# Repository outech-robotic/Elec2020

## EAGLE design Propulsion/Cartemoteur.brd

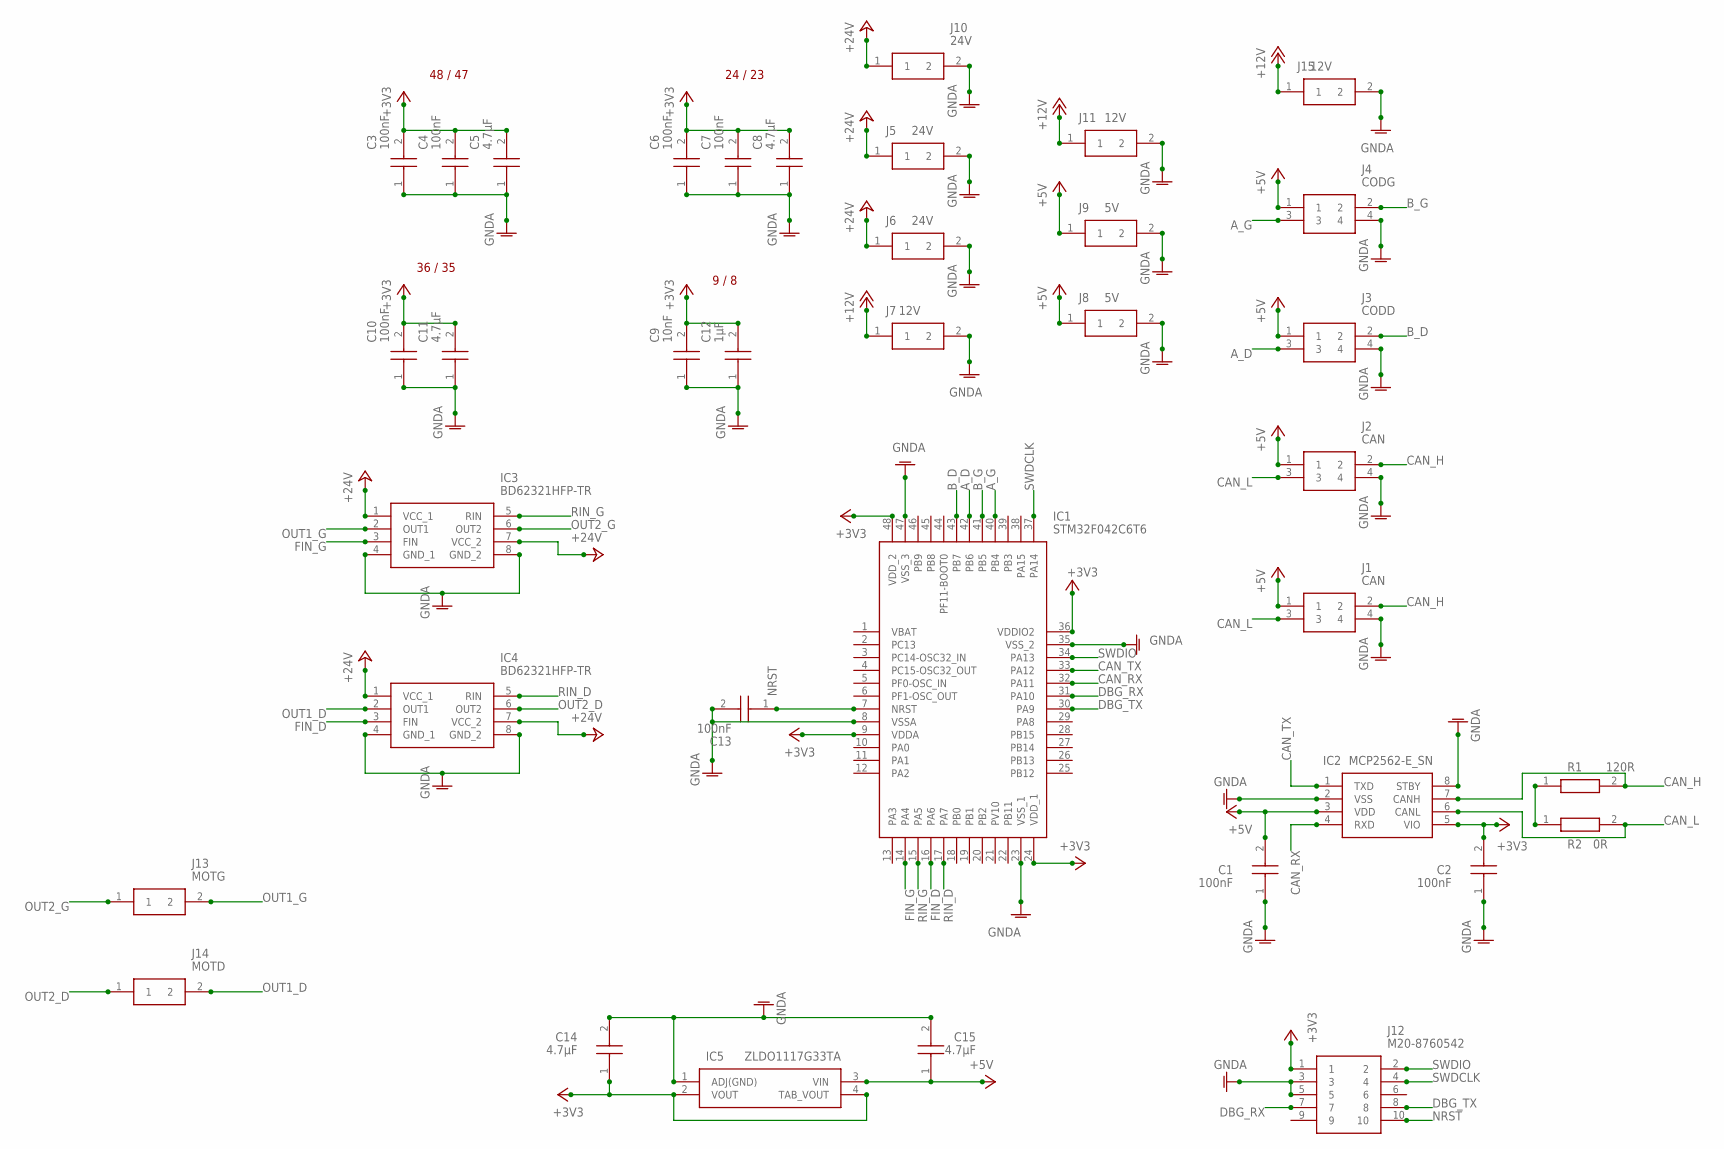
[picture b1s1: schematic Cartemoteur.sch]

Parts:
C1, C2, C3, C4, C6, C7, C10, C13: 100nF; CAPC1608X90N
C5, C8, C11, C14, C15: 4.7µF; CAPC2012X145N
C9: 10nF; CAPC0603X33N
C12: 1µF; CAPC1005X55N
IC1: STM32F042C6T6; QFP50P900X900X160-48N
IC2: MCP2562-E_SN; SOIC127P600X175-8N
IC3, IC4: BD62321HFP-TR; HRP7
IC5: ZLDO1117G33TA; SOT230P700X180-4N
J1, J2: CAN; 436500400
J3: CODD; 436500400
J4: CODG; 436500400
J5, J6, J10: 24V; 43650-0200
J7, J11, J15: 12V; 43650-0200
J8, J9: 5V; 43650-0200
J12: M20-8760542; M208760542
J13: MOTG; 43650-0200
J14: MOTD; 43650-0200
R1: 120R; RESC1608X50N
R2: 0R; RESC1608X55N

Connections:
+3V3: C2.2, C3.2, C4.2, C5.2, C6.2, C7.2, C8.2, C9.2, C10.2, C11.2, C12.2, C14.1, IC1.9 (VDDA), IC1.24 (VDD_1), IC1.36 (VDDIO2), IC1.48 (VDD_2), IC2.5 (VIO), IC5.2 (VOUT), IC5.4 (TAB_VOUT), J12.1
+5V: C1.2, C15.1, IC2.3 (VDD), IC5.3 (VIN), J1.1, J2.1, J3.1, J4.1, J8.1, J9.1
+12V: J7.1, J11.1, J15.1
+24V: IC3.1 (VCC_1), IC3.7 (VCC_2), IC4.1 (VCC_1), IC4.7 (VCC_2), J5.1, J6.1, J10.1
A_D: IC1.42 (PB6), J3.3
A_G: IC1.40 (PB4), J4.3
B_D: IC1.43 (PB7), J3.2
B_G: IC1.41 (PB5), J4.2
CAN_H: IC2.7 (CANH), J1.2, J2.2, R1.2
CAN_L: IC2.6 (CANL), J1.3, J2.3, R2.2
CAN_RX: IC1.32 (PA11), IC2.4 (RXD)
CAN_TX: IC1.33 (PA12), IC2.1 (TXD)
DBG_RX: IC1.31 (PA10), J12.7
DBG_TX: IC1.30 (PA9), J12.8
FIN_D: IC1.16 (PA6), IC4.3 (FIN)
FIN_G: IC1.14 (PA4), IC3.3 (FIN)
GNDA: C1.1, C2.1, C3.1, C4.1, C5.1, C6.1, C7.1, C8.1, C9.1, C10.1, C11.1, C12.1, C13.2, C14.2, C15.2, IC1.8 (VSSA), IC1.23 (VSS_1), IC1.35 (VSS_2), IC1.47 (VSS_3), IC2.2 (VSS), IC2.8 (STBY), IC3.4 (GND_1), IC3.8 (GND_2), IC4.4 (GND_1), IC4.8 (GND_2), IC5.1 (ADJ(GND)), J1.4, J2.4, J3.4, J4.4, J5.2, J6.2, J7.2, J8.2, J9.2, J10.2, J11.2, J12.3, J12.5, J15.2
unnamed: R1.1, R2.1
NRST: C13.1, IC1.7 (NRST), J12.10
OUT1_D: IC4.2 (OUT1), J14.2
OUT1_G: IC3.2 (OUT1), J13.2
OUT2_D: IC4.6 (OUT2), J14.1
OUT2_G: IC3.6 (OUT2), J13.1
RIN_D: IC1.17 (PA7), IC4.5 (RIN)
RIN_G: IC1.15 (PA5), IC3.5 (RIN)
SWDCLK: IC1.37 (PA14), J12.4
SWDIO: IC1.34 (PA13), J12.2

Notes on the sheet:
48 / 47
24 / 23
36 / 35
9 / 8

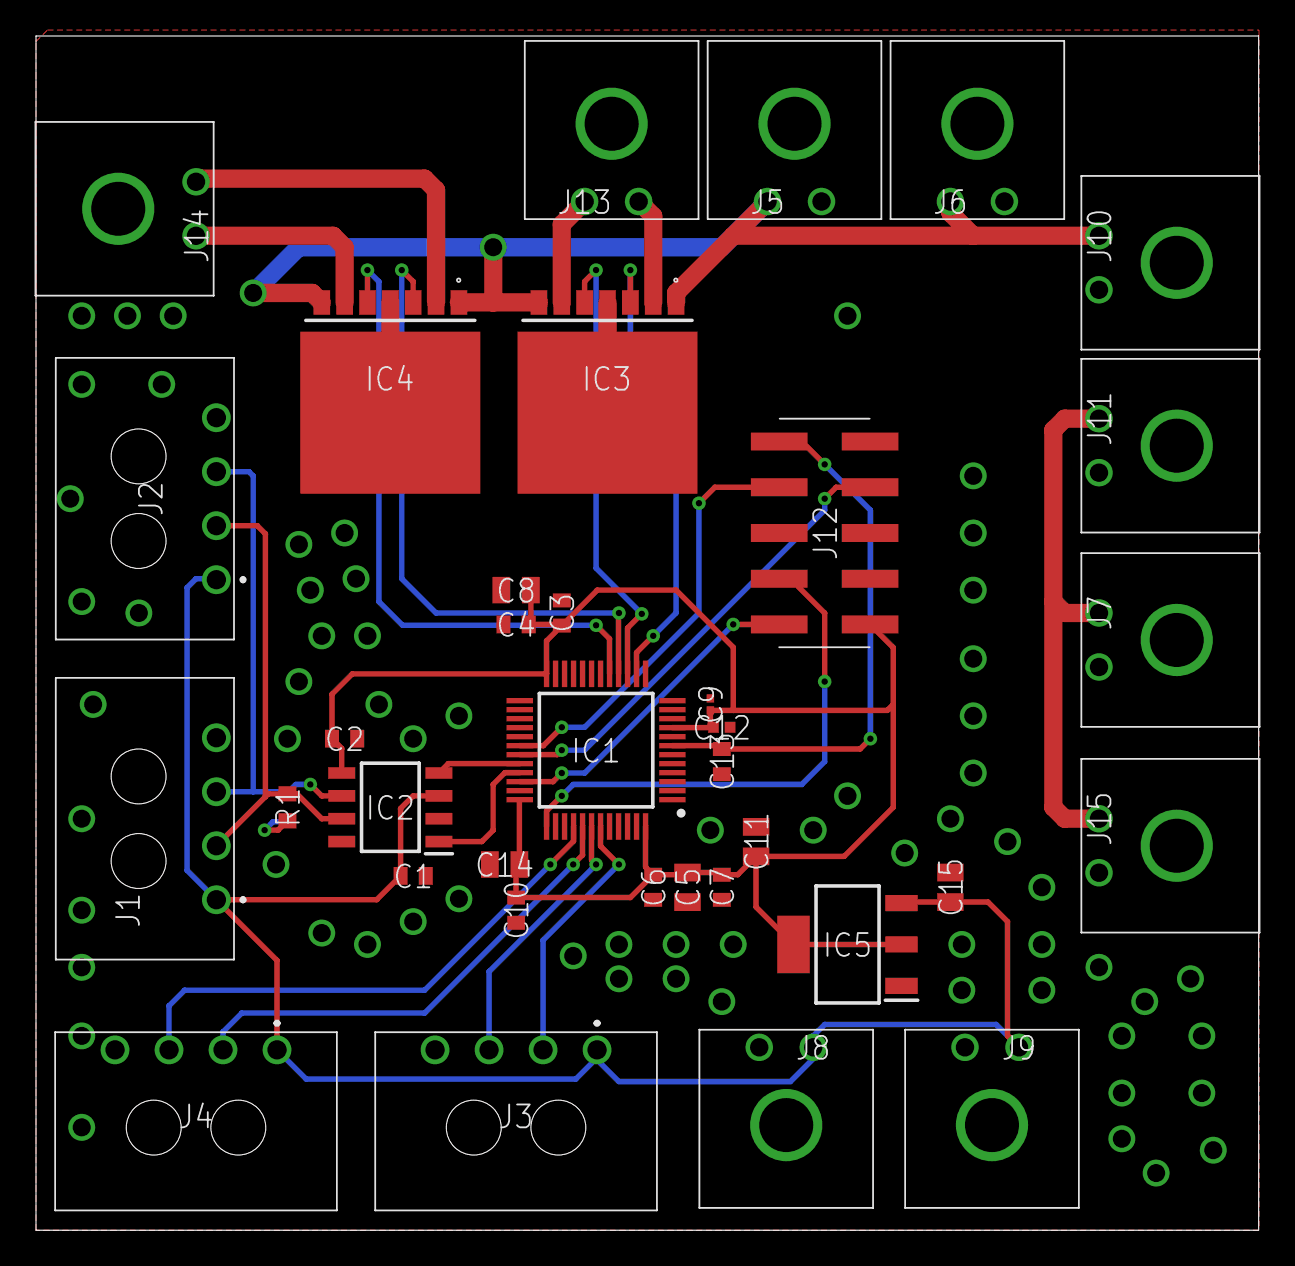
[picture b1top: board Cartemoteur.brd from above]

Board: 2 copper layers, 67.9 x 66.3 mm, 37 parts (1 on the bottom side), 27 nets.

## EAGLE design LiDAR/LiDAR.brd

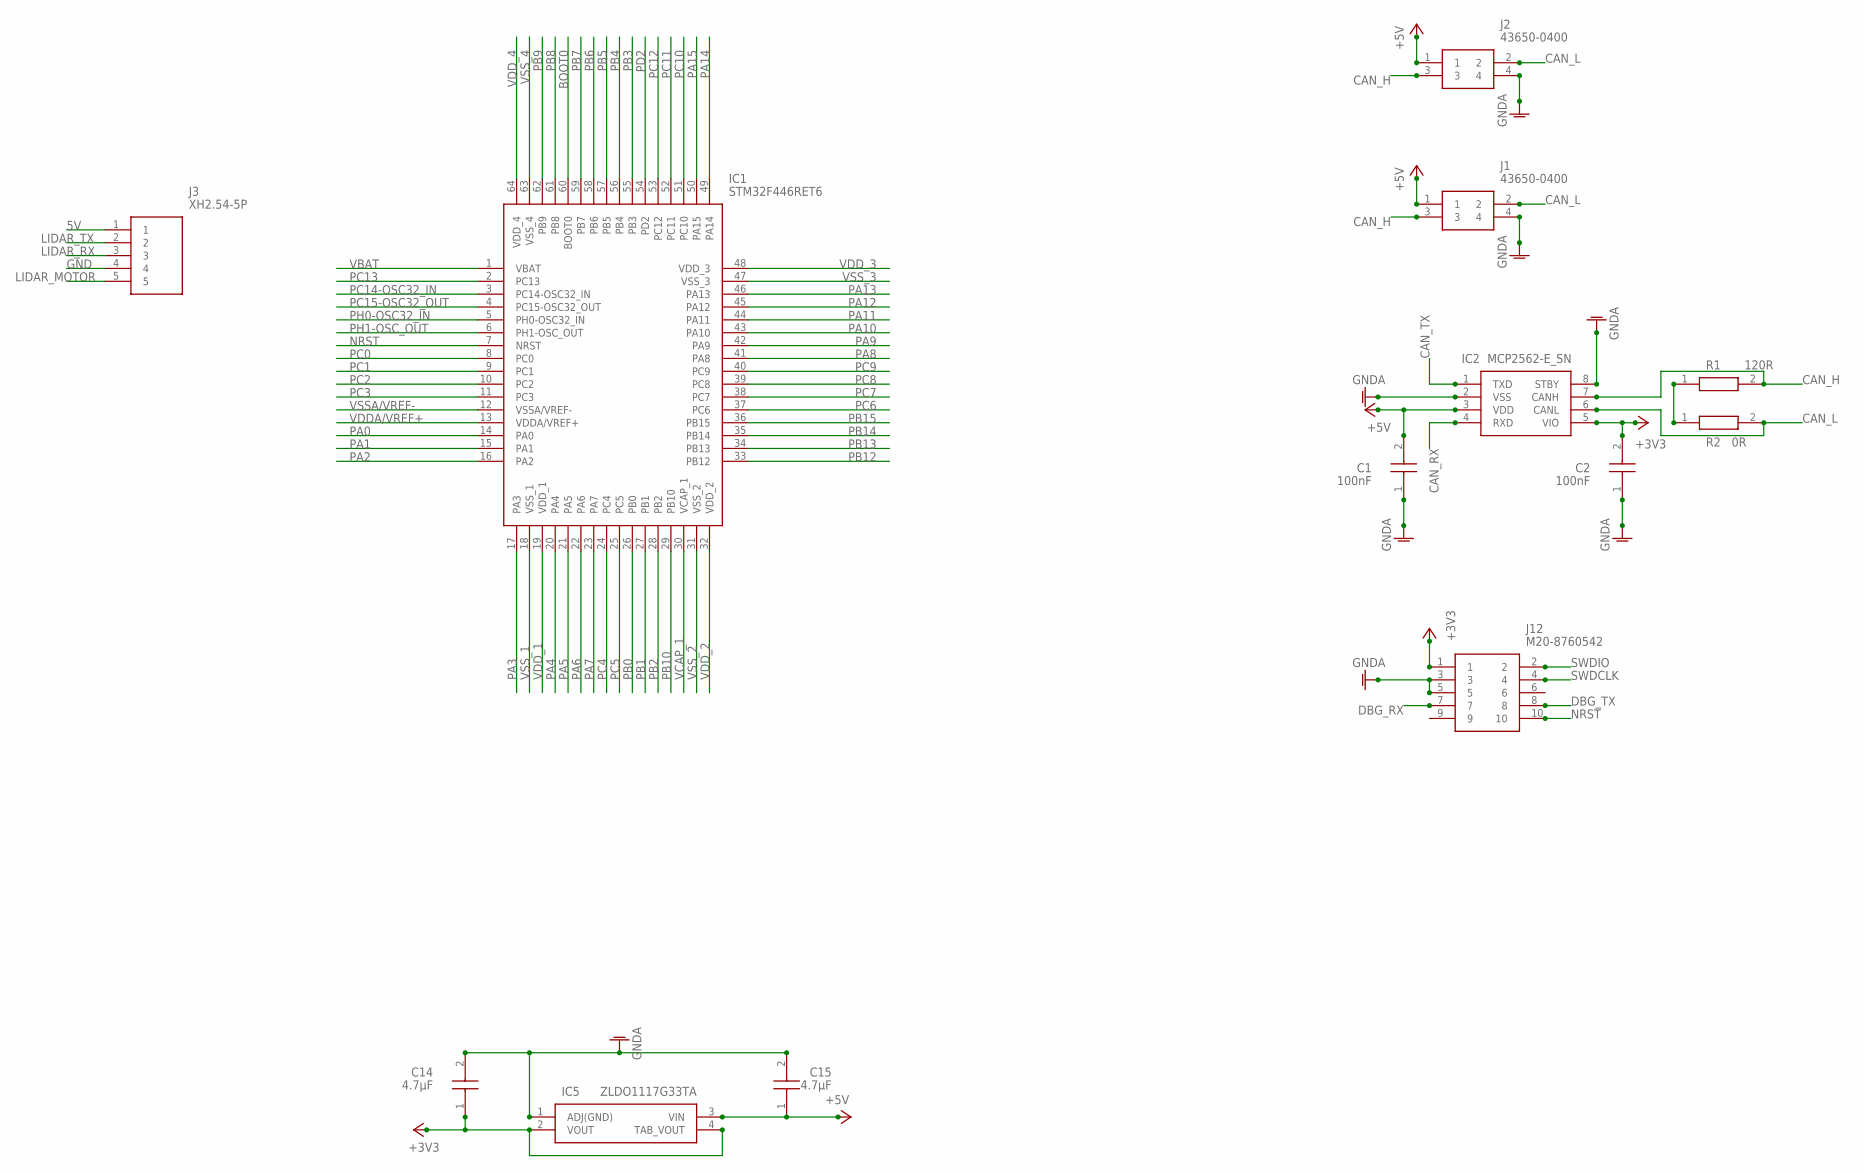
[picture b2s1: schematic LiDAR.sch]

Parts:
C1, C2: 100nF; CAPC1608X90N
C14, C15: 4.7µF; CAPC2012X145N
IC1: STM32F446RET6; QFP50P1200X1200X160-64N
IC2: MCP2562-E_SN; SOIC127P600X175-8N
IC5: ZLDO1117G33TA; SOT230P700X180-4N
J1, J2: 43650-0400; 436500400
J3: XH2.54-5P; SHDR5W64P0X250_1X5_1490X575X70
J12: M20-8760542; M208760542
R1: 120R; RESC1608X50N
R2: 0R; RESC1608X55N

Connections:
5V: J3.1
+3V3: C2.2, C14.1, IC2.5 (VIO), IC5.2 (VOUT), IC5.4 (TAB_VOUT), J12.1
+5V: C1.2, C15.1, IC2.3 (VDD), IC5.3 (VIN), J1.1, J2.1
BOOT0: IC1.60 (BOOT0)
CAN_H: IC2.7 (CANH), J1.3, J2.3, R1.2
CAN_L: IC2.6 (CANL), J1.2, J2.2, R2.2
CAN_RX: IC2.4 (RXD)
CAN_TX: IC2.1 (TXD)
DBG_RX: J12.7
DBG_TX: J12.8
GND: J3.4
GNDA: C1.1, C2.1, C14.2, C15.2, IC2.2 (VSS), IC2.8 (STBY), IC5.1 (ADJ(GND)), J1.4, J2.4, J12.3, J12.5
LIDAR_MOTOR: J3.5
LIDAR_RX: J3.3
LIDAR_TX: J3.2
unnamed: R1.1, R2.1
NRST: IC1.7 (NRST), J12.10
PA0: IC1.14 (PA0)
PA1: IC1.15 (PA1)
PA2: IC1.16 (PA2)
PA3: IC1.17 (PA3)
PA4: IC1.20 (PA4)
PA5: IC1.21 (PA5)
PA6: IC1.22 (PA6)
PA7: IC1.23 (PA7)
PA8: IC1.41 (PA8)
PA9: IC1.42 (PA9)
PA10: IC1.43 (PA10)
PA11: IC1.44 (PA11)
PA12: IC1.45 (PA12)
PA13: IC1.46 (PA13)
PA14: IC1.49 (PA14)
PA15: IC1.50 (PA15)
PB0: IC1.26 (PB0)
PB1: IC1.27 (PB1)
PB2: IC1.28 (PB2)
PB3: IC1.55 (PB3)
PB4: IC1.56 (PB4)
PB5: IC1.57 (PB5)
PB6: IC1.58 (PB6)
PB7: IC1.59 (PB7)
PB8: IC1.61 (PB8)
PB9: IC1.62 (PB9)
PB10: IC1.29 (PB10)
PB12: IC1.33 (PB12)
PB13: IC1.34 (PB13)
PB14: IC1.35 (PB14)
PB15: IC1.36 (PB15)
PC0: IC1.8 (PC0)
PC1: IC1.9 (PC1)
PC2: IC1.10 (PC2)
PC3: IC1.11 (PC3)
PC4: IC1.24 (PC4)
PC5: IC1.25 (PC5)
PC6: IC1.37 (PC6)
PC7: IC1.38 (PC7)
PC8: IC1.39 (PC8)
PC9: IC1.40 (PC9)
PC10: IC1.51 (PC10)
PC11: IC1.52 (PC11)
PC12: IC1.53 (PC12)
PC13: IC1.2 (PC13)
PC14-OSC32_IN: IC1.3 (PC14-OSC32_IN)
PC15-OSC32_OUT: IC1.4 (PC15-OSC32_OUT)
PD2: IC1.54 (PD2)
PH0-OSC32_IN: IC1.5 (PH0-OSC32_IN)
PH1-OSC_OUT: IC1.6 (PH1-OSC_OUT)
SWDCLK: J12.4
SWDIO: J12.2
VBAT: IC1.1 (VBAT)
VCAP_1: IC1.30 (VCAP_1)
VDDA/VREF+: IC1.13 (VDDA/VREF+)
VDD_1: IC1.19 (VDD_1)
VDD_2: IC1.32 (VDD_2)
VDD_3: IC1.48 (VDD_3)
VDD_4: IC1.64 (VDD_4)
VSSA/VREF-: IC1.12 (VSSA/VREF-)
VSS_1: IC1.18 (VSS_1)
VSS_2: IC1.31 (VSS_2)
VSS_3: IC1.47 (VSS_3)
VSS_4: IC1.63 (VSS_4)

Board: 2 copper layers, 13 parts (0 on the bottom side), 7 nets, no tracks yet.

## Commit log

2019-08-19 First commit, adding brushed motor PCB
2019-08-19 adding lib and first pcb for brushed motors
2019-08-19 ajout projet lidar, connecteur et stm32f446 dans la lib
2019-08-21 BOARD V1
